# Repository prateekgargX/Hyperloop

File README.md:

# Hyperloop
 Stuff I did as Jr. Controls Engineer at Hyperloop IITB

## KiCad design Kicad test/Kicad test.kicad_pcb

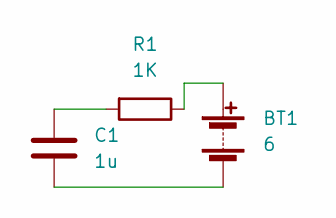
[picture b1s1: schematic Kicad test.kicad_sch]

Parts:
BT1: 6; BatteryHolder_Keystone_103_1x20mm
C1: 1u; CP_Elec_5x5.4
R1: 1K; R_Axial_DIN0204_L3.6mm_D1.6mm_P5.08mm_Vertical

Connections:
unnamed: BT1.1 (+), R1.1
unnamed: BT1.2 (-), C1.2
unnamed: C1.1, R1.2

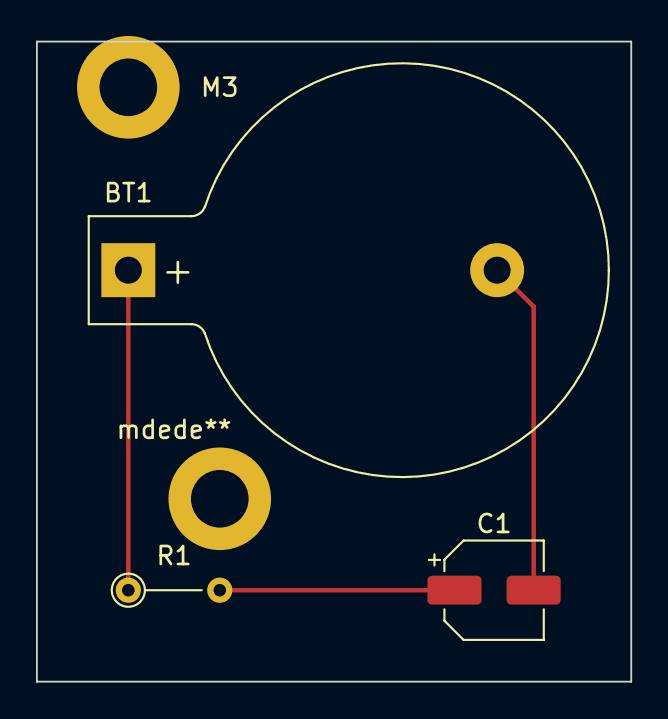
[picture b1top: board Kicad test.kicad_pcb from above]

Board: 2 copper layers, 33.0 x 35.6 mm, 5 parts (0 on the bottom side), 3 nets.

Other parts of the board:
M3: MountingHole_3.2mm_M3_ISO7380_Pad
mdede**: MountingHole_3.2mm_M3_ISO7380_Pad

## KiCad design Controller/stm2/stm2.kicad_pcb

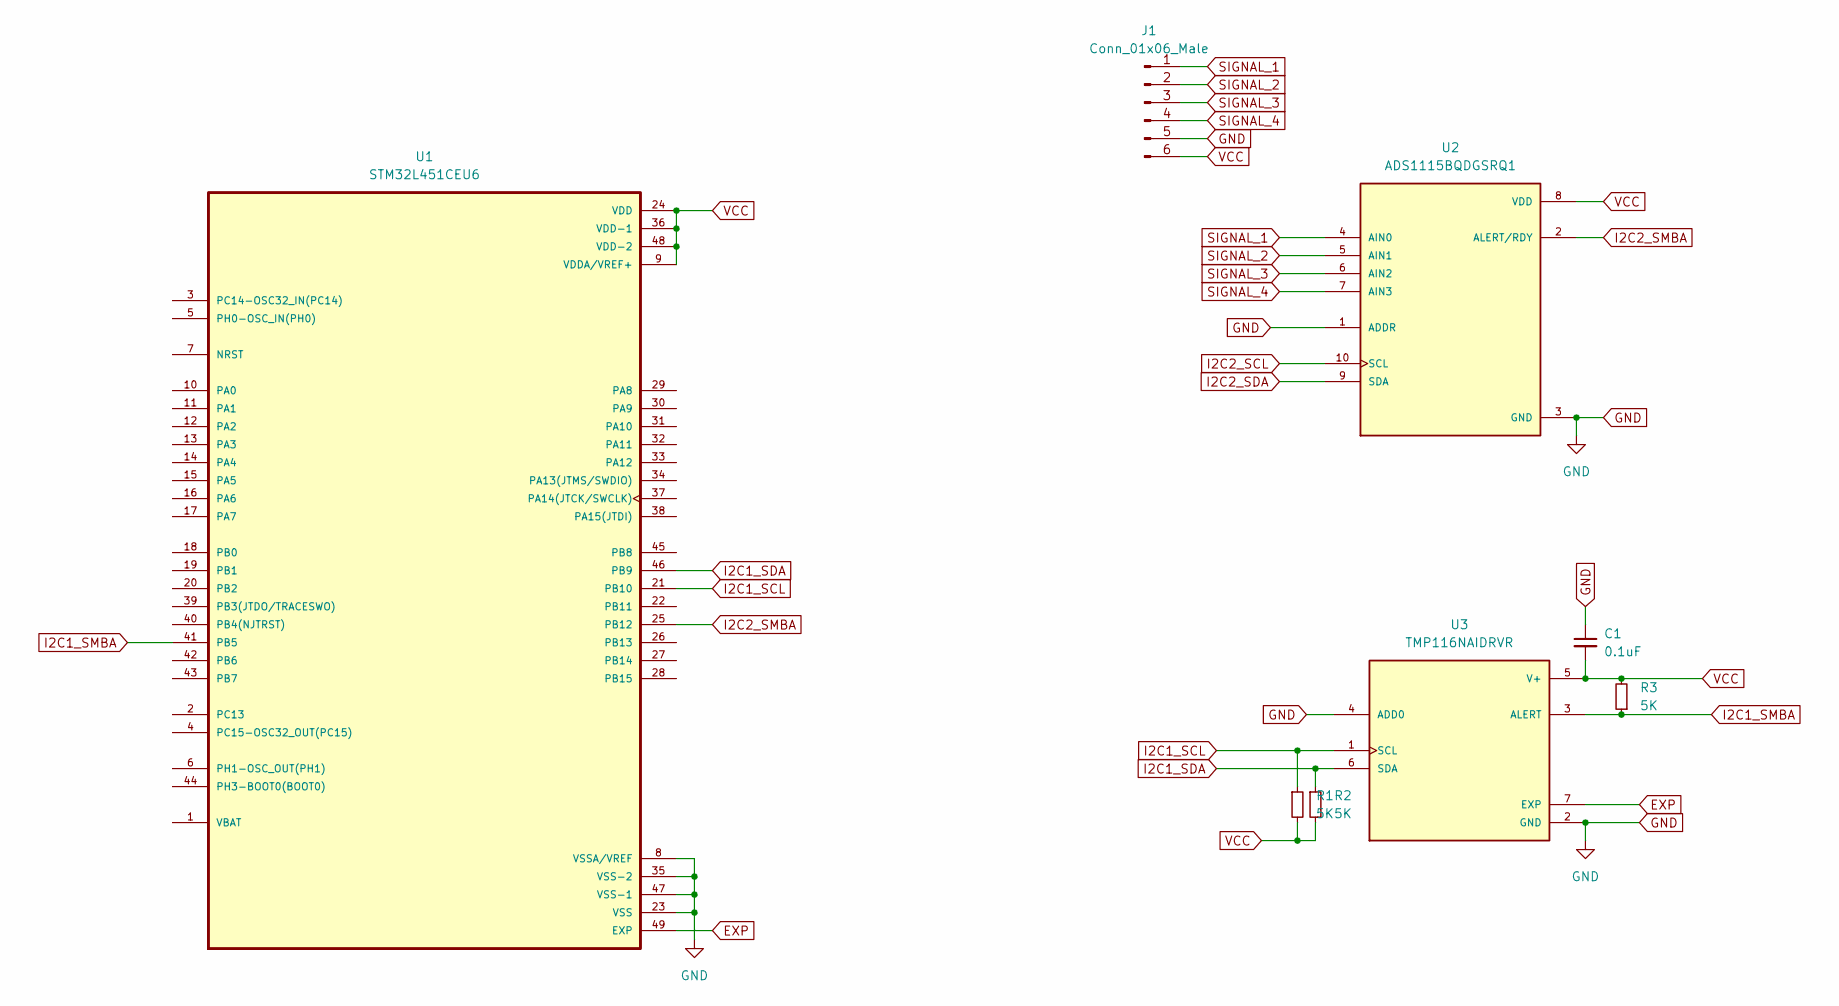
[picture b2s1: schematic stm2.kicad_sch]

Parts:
C1: 0.1uF; C_0603_1608Metric_Pad1.08x0.95mm_HandSolder
J1: Conn_01x06_Male; PinHeader_1x06_P2.54mm_Vertical
R1, R2, R3: 5K; R_0603_1608Metric_Pad0.98x0.95mm_HandSolder
U1: STM32L451CEU6; QFN50P700X700X60-49N; PARTREV Rev 4
U2: ADS1115BQDGSRQ1; SOP50P490X110-10N; PARTREV D
U3: TMP116NAIDRVR; SON65P200X200X80-7N; PARTREV Rev. A

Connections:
EXP: U1.49 (EXP), U3.7 (EXP)
GND: C1.1, J1.5, U1.8 (VSSA/VREF), U1.23 (VSS), U1.35 (VSS-2), U1.47 (VSS-1), U2.1 (ADDR), U2.3 (GND), U3.2 (GND), U3.4 (ADD0)
I2C1_SCL: R1.1, U1.21 (PB10), U3.1 (SCL)
I2C1_SDA: R2.1, U1.46 (PB9), U3.6 (SDA)
I2C1_SMBA: R3.1, U1.41 (PB5), U3.3 (ALERT)
I2C2_SCL: U2.10 (SCL)
I2C2_SDA: U2.9 (SDA)
I2C2_SMBA: U1.25 (PB12), U2.2 (ALERT/RDY)
SIGNAL_1: J1.1, U2.4 (AIN0)
SIGNAL_2: J1.2, U2.5 (AIN1)
SIGNAL_3: J1.3, U2.6 (AIN2)
SIGNAL_4: J1.4, U2.7 (AIN3)
VCC: C1.2, J1.6, R1.2, R2.2, R3.2, U1.9 (VDDA/VREF+), U1.24 (VDD), U1.36 (VDD-1), U1.48 (VDD-2), U2.8 (VDD), U3.5 (V+)

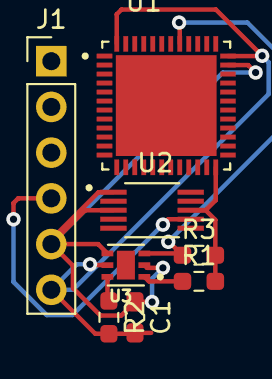
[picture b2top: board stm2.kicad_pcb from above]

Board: 2 copper layers, 8 parts (0 on the bottom side), 11 nets.

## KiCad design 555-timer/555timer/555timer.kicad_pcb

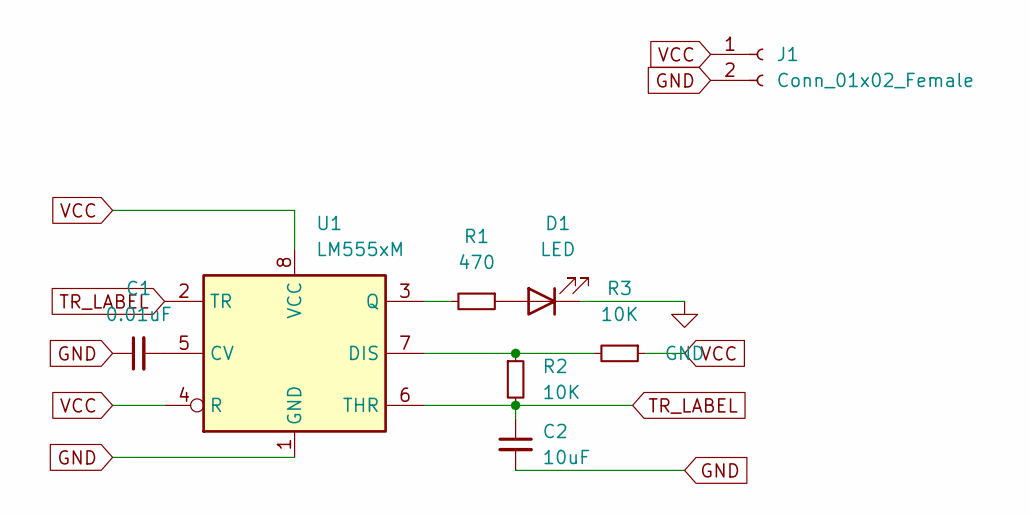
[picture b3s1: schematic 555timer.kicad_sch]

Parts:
C1: 0.01uF; C_0504_1310Metric_Pad0.83x1.28mm_HandSolder
C2: 10uF; C_0504_1310Metric_Pad0.83x1.28mm_HandSolder
D1: LED; LED_D1.8mm_W1.8mm_H2.4mm_Horizontal_O1.27mm_Z8.2mm
J1: Conn_01x02_Female; PinHeader_1x02_P1.00mm_Horizontal
R1: 470; R_Axial_DIN0204_L3.6mm_D1.6mm_P7.62mm_Horizontal
R2, R3: 10K; R_Axial_DIN0204_L3.6mm_D1.6mm_P7.62mm_Horizontal
U1: LM555xM; SOIC-8_3.9x4.9mm_P1.27mm

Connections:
GND: C1.1, C2.2, D1.1 (K), J1.2, U1.1 (GND)
unnamed: C1.2, U1.5 (CV)
unnamed: D1.2 (A), R1.1
unnamed: R1.2, U1.3 (Q)
unnamed: R2.1, R3.2, U1.7 (DIS)
TR_LABEL: C2.1, R2.2, U1.2 (TR), U1.6 (THR)
VCC: J1.1, R3.1, U1.4 (R), U1.8 (VCC)

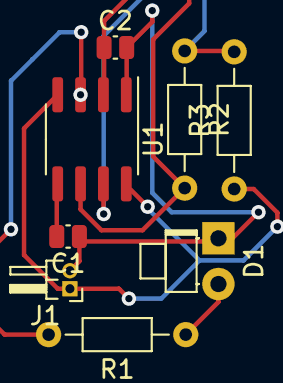
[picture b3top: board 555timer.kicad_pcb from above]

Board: 2 copper layers, 8 parts (0 on the bottom side), 7 nets.

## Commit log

2021-11-27 Data for Alpha-Beta Filter
2021-11-27 Add task-list
2021-11-27 Task-0.1
2021-11-27 README.md patch-4
2021-11-28 AlphaBeta filter complete
2021-11-28 AlphaBetaGamma-1
2021-11-28 ABG lag
2021-11-28 done with second filter
2021-11-28 deleted weird file
2021-11-28 Task-1 final commit
2021-12-04 Experiment
2021-12-04 Percentage error
2021-12-04 Convergence metric
2021-12-14 hrthr
2021-12-14 Problem Statements and Datasheets
2021-12-14 Noise on Alpha-Beta-Gamma Filter
2021-12-19 Add Data with process noise
2021-12-19 create KF with process noise
2021-12-19 Add Data for heating liquid
2021-12-19 Add Heating Liquid
2021-12-20 probStatI
2021-12-20 Complete the assignment
2021-12-20 Phew
2022-05-26 Final commit
    Hopefully
